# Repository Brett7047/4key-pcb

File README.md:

# 4key-pcb
Creating my first pcb in kicad for a 4-key keyboard. Using as an example to springboard into designing a full keyboard

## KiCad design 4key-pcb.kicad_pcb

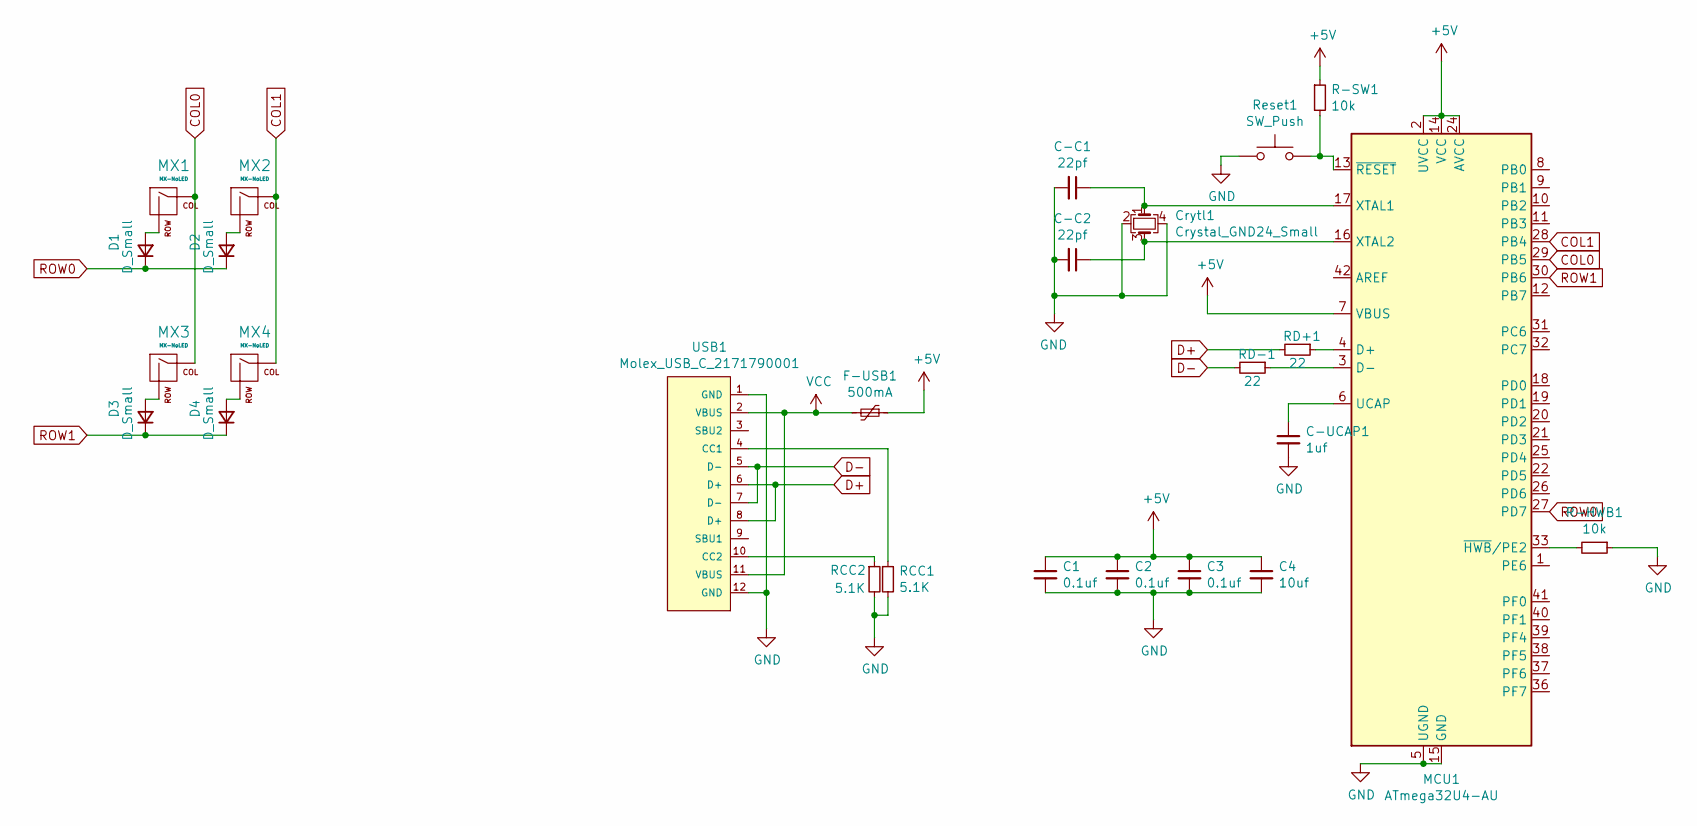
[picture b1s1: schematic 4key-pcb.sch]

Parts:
C1: 0.1uf; C_0805_2012Metric_Pad1.18x1.45mm_HandSolder
C2, C3: 0.1uf; C_0805_2012Metric
C4: 10uf; C_0805_2012Metric
C-C1, C-C2: 22pf; C_0805_2012Metric
C-UCAP1: 1uf; C_0805_2012Metric
Crytl1: Crystal_GND24_Small; Crystal_SMD_3225-4Pin_3.2x2.5mm
D1, D2, D3, D4: D_Small; D_SOD-123
F-USB1: 500mA; Fuse_1206_3216Metric
MCU1: ATmega32U4-AU; TQFP-44_10x10mm_P0.8mm
MX1, MX2, MX3, MX4: MX-NoLED; MX-1U-NoLED
R-HWB1: 10k; R_0805_2012Metric
R-SW1: 10k; R_0805_2012Metric
RCC1, RCC2: 5.1K; R_0805_2012Metric
RD+1: 22; R_0805_2012Metric
RD-1: 22; R_0805_2012Metric
Reset1: SW_Push; SKQG-1155865
USB1: Molex_USB_C_2171790001; Molex_USB-C_2171790001

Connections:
+5V: C1.1, C2.1, C3.1, C4.1, F-USB1.1, MCU1.2 (UVCC), MCU1.7 (VBUS), MCU1.14 (VCC), MCU1.24 (AVCC), MCU1.34 (VCC), MCU1.44 (AVCC), R-SW1.1
COL0: MCU1.29 (PB5), MX1.1 (COL), MX3.1 (COL)
COL1: MCU1.28 (PB4), MX2.1 (COL), MX4.1 (COL)
D+: RD+1.2, USB1.6 (D+), USB1.8 (D+)
D-: RD-1.2, USB1.5 (D-), USB1.7 (D-)
GND: C1.2, C2.2, C3.2, C4.2, C-C1.2, C-C2.2, C-UCAP1.2, Crytl1.2, Crytl1.4, MCU1.5 (UGND), MCU1.15 (GND), MCU1.23 (GND), MCU1.35 (GND), MCU1.43 (GND), R-HWB1.1, RCC1.2, RCC2.2, Reset1.1, USB1.1 (GND), USB1.12 (GND)
unnamed: C-C1.1, Crytl1.1, MCU1.17 (XTAL1)
unnamed: C-C2.1, Crytl1.3, MCU1.16 (XTAL2)
unnamed: C-UCAP1.1, MCU1.6 (UCAP)
unnamed: D1.2 (A), MX1.2 (ROW)
unnamed: D2.2 (A), MX2.2 (ROW)
unnamed: D3.2 (A), MX3.2 (ROW)
unnamed: D4.2 (A), MX4.2 (ROW)
unnamed: MCU1.3 (D-), RD-1.1
unnamed: MCU1.4 (D+), RD+1.1
unnamed: MCU1.13 (~RESET), R-SW1.2, Reset1.2
unnamed: MCU1.33 (~HWB~/PE2), R-HWB1.2
unnamed: RCC1.1, USB1.4 (CC1)
unnamed: RCC2.1, USB1.10 (CC2)
ROW0: D1.1 (K), D2.1 (K), MCU1.27 (PD7)
ROW1: D3.1 (K), D4.1 (K), MCU1.30 (PB6)
VCC: F-USB1.2, USB1.2 (VBUS), USB1.11 (VBUS)

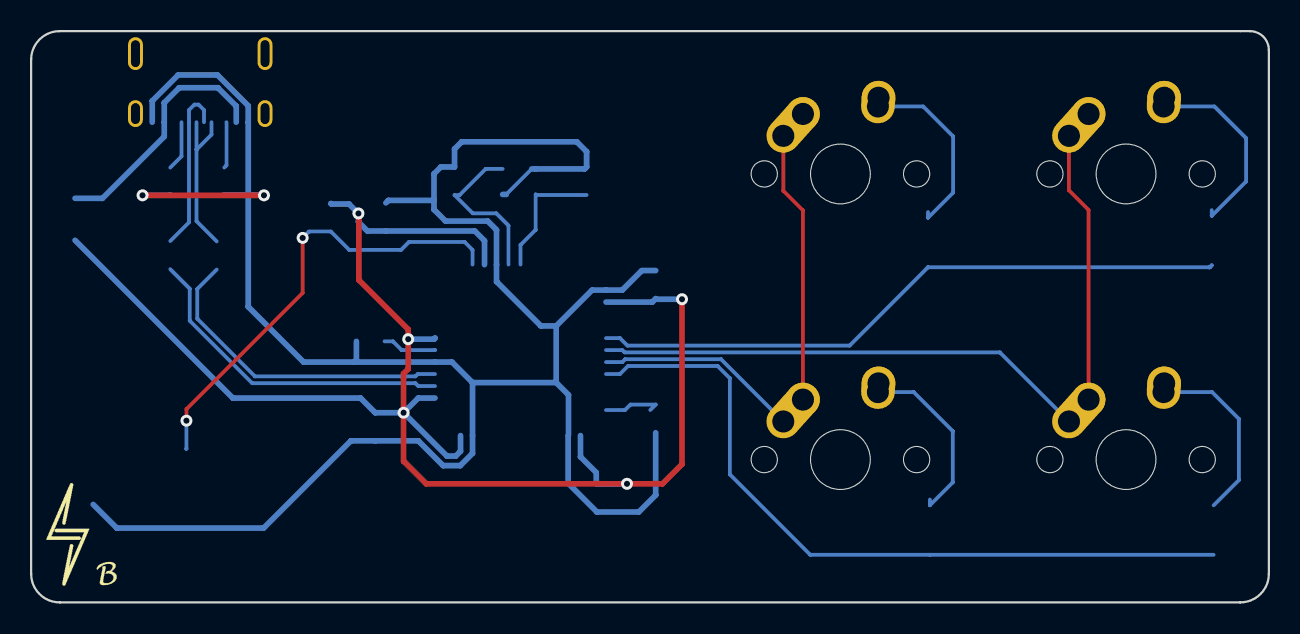
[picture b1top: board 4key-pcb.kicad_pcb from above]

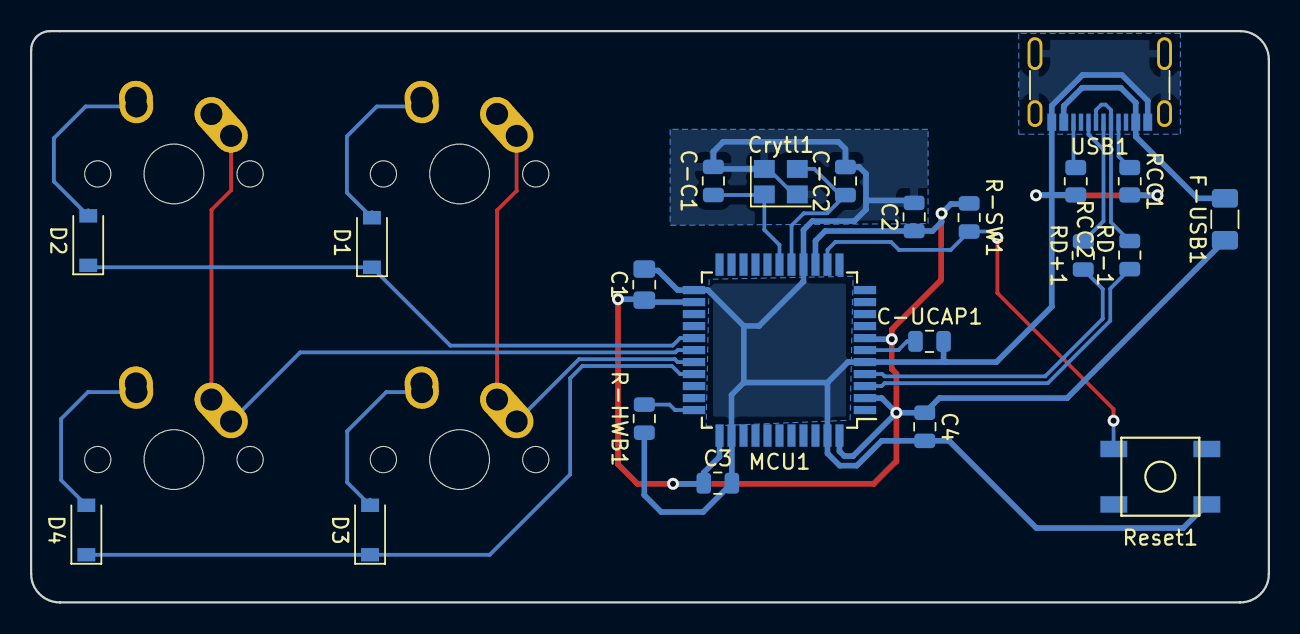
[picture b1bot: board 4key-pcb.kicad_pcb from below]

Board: 2 copper layers, 82.6 x 38.1 mm, 26 parts (22 on the bottom side), 22 nets.

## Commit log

2020-12-16 initialized kicad pcb
2020-12-16 addes submodules for switch + usb footprints
2020-12-16 added project specific libraries
2020-12-16 begun eeschema
2020-12-16 finished eeschema
2020-12-17 finished usb, switches and applied footprints
2020-12-17 initial design of pcb
2020-12-24 started routing traces
2020-12-25 finished routing mcu
2020-12-25 finished pcb routing
2020-12-26 added inkscape logo + footprint
2020-12-26 finished pcb
2020-12-31 added more keyboard footprints
2021-01-06 finally fixed footprint error
2021-07-23 updated to usb-c
2021-07-26 export to geber for pcb
2021-07-26 usb-c conn datasheet
2021-07-26 final
